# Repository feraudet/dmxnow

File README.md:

# dmxnow

Wireless DMX and LED strip nodes over ESP-NOW, driven by QLC+ from a Raspberry Pi.
One mains cable per fixture: DMX arrives by radio, the node switches the fixture's
power and drives 4 LED strip channels.

Nœuds DMX et rubans LED sans fil, sur ESP-NOW, pilotés par QLC+ depuis un Raspberry Pi.
Un seul câble secteur par projecteur : le DMX arrive par radio, le nœud coupe
l'alimentation du projecteur et pilote 4 canaux de rubans LED.

| | |
|---|---|
| 🇬🇧 **[Read in English](README.en.md)** | context, the need, use cases, how it works, status |
| 🇫🇷 **[Lire en français](README.fr.md)** | contexte, besoin, cas d'usage, fonctionnement, état du projet |

🔴 230 V mains device: read [docs/securite.md](docs/securite.md) first.
Appareil raccordé au 230 V : lire [docs/securite.md](docs/securite.md) avant tout.

Hardware CERN-OHL-S-2.0, software GPL-3.0-or-later: [LICENSE](LICENSE).

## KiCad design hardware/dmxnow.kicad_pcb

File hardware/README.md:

# dmxnow : matériel

PCB du nœud : 2 couches, cuivre 2 oz, **146 × 54 mm** plus une bande de 47,5 × 11,5 mm
au-dessus de la zone 230 V (porte-fusible F1), séparation à X = 100 mm par fente fraisée
et trois languettes perforées (partie principale « projecteur » 100 × 54 mm, partie
sécable « rubans » 46 × 54 mm). Révision 0.3 (après revue de conception, voir
`REVIEW.md`).

> 🔴 Carte manipulant du 230 V : lire et compléter [REVIEW.md](REVIEW.md) avant toute
> commande ou mise sous tension. Les cotes de K1 (Omron G5RL-1A-E-HR), des borniers WAGO
> 2604 et de PS1 (Mean Well IRM-03-5) ont été relevées sur les fiches constructeur
> ([datasheets/README.md](datasheets/README.md)) ; leur contrôle fait partie de la relecture.

## Contenu

| Fichier | Rôle |
|---------|------|
| `gen/design.py` | **Source unique** : composants, empreintes, broches → nets, classes de nets |
| `gen/footprints.py` | Empreintes du projet (`lib/dmxnow.pretty`), cotes et sources dans `DIMS` |
| `gen/sch.py` | Génère `dmxnow.kicad_sch` (schéma à étiquettes, symboles embarqués) |
| `gen/project.py` | Génère `dmxnow.kicad_pro` (classes de nets) et `dmxnow.kicad_dru` (règles 230 V) |
| `gen/pcb.py` | Génère `dmxnow.kicad_pcb` : contour, fentes, languettes perforées, placement, routage 230 V et LED, plans |
| `gen/route.py` | Routage des signaux basse tension par Freerouting, vias d'échappement et de couture GND |
| `gen/fixup.py` | Passe de finition : ferme les liaisons laissées par le routeur (segments directs, vias vers les plans) |
| `gen/vendor.py` | Copie figée des symboles et empreintes KiCad utilisés (`lib/vendor/`) |
| `gen/check.py` | Contrôles de cohérence : netlist du schéma, pastilles du PCB, traversée de la découpe |
| `gen/drc.py` | DRC local via l'API pcbnew (KiCad 7+) |
| `gen/fab.py` | Sorties JLCPCB dans `fab/` |
| `lib/` | Bibliothèques : `dmxnow.pretty`, `Espressif.*` (espressif/kicad-libraries, CC-BY-SA 4.0) |
| `REVIEW.md` | Liste de contrôle de la relecture humaine |
| `revision-suivante.md` | Points à intégrer à la prochaine révision du PCB |

Ne pas éditer les fichiers KiCad à la main : modifier les scripts et régénérer (un
changement manuel serait écrasé et rendrait la CI rouge).

## Régénérer

Prérequis : KiCad ≥ 7 (module Python `pcbnew`, `kicad-cli`), Java ≥ 17, Freerouting
(`FREEROUTING_JAR`, défaut `/opt/freerouting/freerouting.jar`).

```sh
cd hardware
make lib sch project   # empreintes, schéma, projet et règles
make pcb route         # PCB puis routage automatique + finition (~15 min)
make check             # netlist, cohérence PCB, DRC local
make fab               # Gerbers, perçages, BOM/CPL JLCPCB
```

`make pcb` repart de zéro : il faut relancer `make route` ensuite (ou `make reimport`
pour réappliquer la dernière session Freerouting si aucun composant n'a bougé).
Freerouting n'est pas déterministe : deux passages donnent des routages différents,
toujours validés par `make check`.

## Contrôles

- **Local** (KiCad 7) : `make check` (netlist schéma = `design.py`, pastilles PCB =
  `design.py`, seuls PWM1-4, BOARD_SENSE, +5V, GND traversent la découpe et uniquement
  sur les languettes, aucune piste 230 V au-delà de X = 46 mm, aucun via dans une
  pastille CMS, DRC, puis `gen/drc_canary.py` : des défauts injectés doivent déclencher
  chaque règle 230 V, preuve que les règles personnalisées sont chargées).
- **CI** (`.github/workflows/hardware.yml`, KiCad 9) : fichiers générés à jour, ERC, DRC
  avec parité schéma/PCB, sorties de fabrication, rendus 3D dessus/dessous (artefact
  `dmxnow-hardware`).

## Règles d'isolement (🔴)

Définies dans `gen/project.py` → `dmxnow.kicad_dru` :

| Règle | Valeur |
|-------|--------|
| Cuivre 230 V ↔ tout autre cuivre ou trou | ≥ 6 mm |
| Entre nets 230 V | ≥ 3 mm |
| Pastilles internes de K1 (COM/NO) et de PS1 (AC) | ≥ 2 mm (imposé par le composant) |
| Cuivre 230 V ↔ bord de carte | ≥ 1 mm |

Géométrie : cuivre 230 V à X ≤ 46 mm, basse tension à X ≥ 52 mm, fentes de 1,2 mm à
X = 49 mm sous K1 et PS1, aucun cuivre à moins de 6 mm de la pastille NC de PS1 (rangée
AC du module). Aucun trou de fixation dans la zone 230 V. Le PE ne passe pas
par la carte (WAGO 221-413 dans le boîtier, arbitrage A9).

## Commande JLCPCB

Dossier pas à pas (réglages, remarque, aperçu, achats hors JLCPCB) : [`ORDER.md`](ORDER.md).

- `fab/dmxnow-gerbers.zip` : 2 couches, 1,6 mm, **2 oz**, FR-4 TG ≥ 150.
- Séparation : fente et perforations sont dans les Gerbers (Edge.Cuts, NPTH). JLCPCB
  compte la carte comme **2 designs** : « Different Design = 2 », « Panel by Customer »
  1×1, « Remove order number = Yes ». Remarque de commande :
  « One circuit with an internal routed slot and 3 breakaway tabs carrying traces; deliver and assemble as one piece, do NOT separate. SMT: convey on the straight short edges X=0 and X=146; U1/Q5/R10 are close to the Y=54 edge by design. J3, J2 not populated: keep holes open (no solder fill). J1, J4, J7, J5, J6, J8: wire entry toward board edge; J6 and J8 side by side. RV1: form leads to the PCB holes. F2: press flat before soldering. F1/F2 fuses are not fitted. »
- Assemblage complet (CMS + traversants, PCBA « Standard ») : `fab/bom_jlcpcb_full.csv`
  + `fab/cpl_jlcpcb_full.csv` ; CMS seuls (PCBA « Economic », traversants à la main) :
  `*_smt.csv`. Suffixe `_led` : avec la LED d'état (option A7). Positions et rotations
  converties aux conventions JLCPCB (`gen/fab.py`, `JLC_FIX`) ; contrôler l'aperçu de
  placement à la commande. Références LCSC vérifiées le 2026-09-26 (le WAGO 2604-1105 arrêté est
  remplacé par J6 2604-1102 + J8 2604-1103). La cartouche de F1 (Littelfuse 0215.500MXP) et le fusible de F2
  sont à insérer à la main.
- Composants traversants et hors carte : `fab/bom_full.csv`.

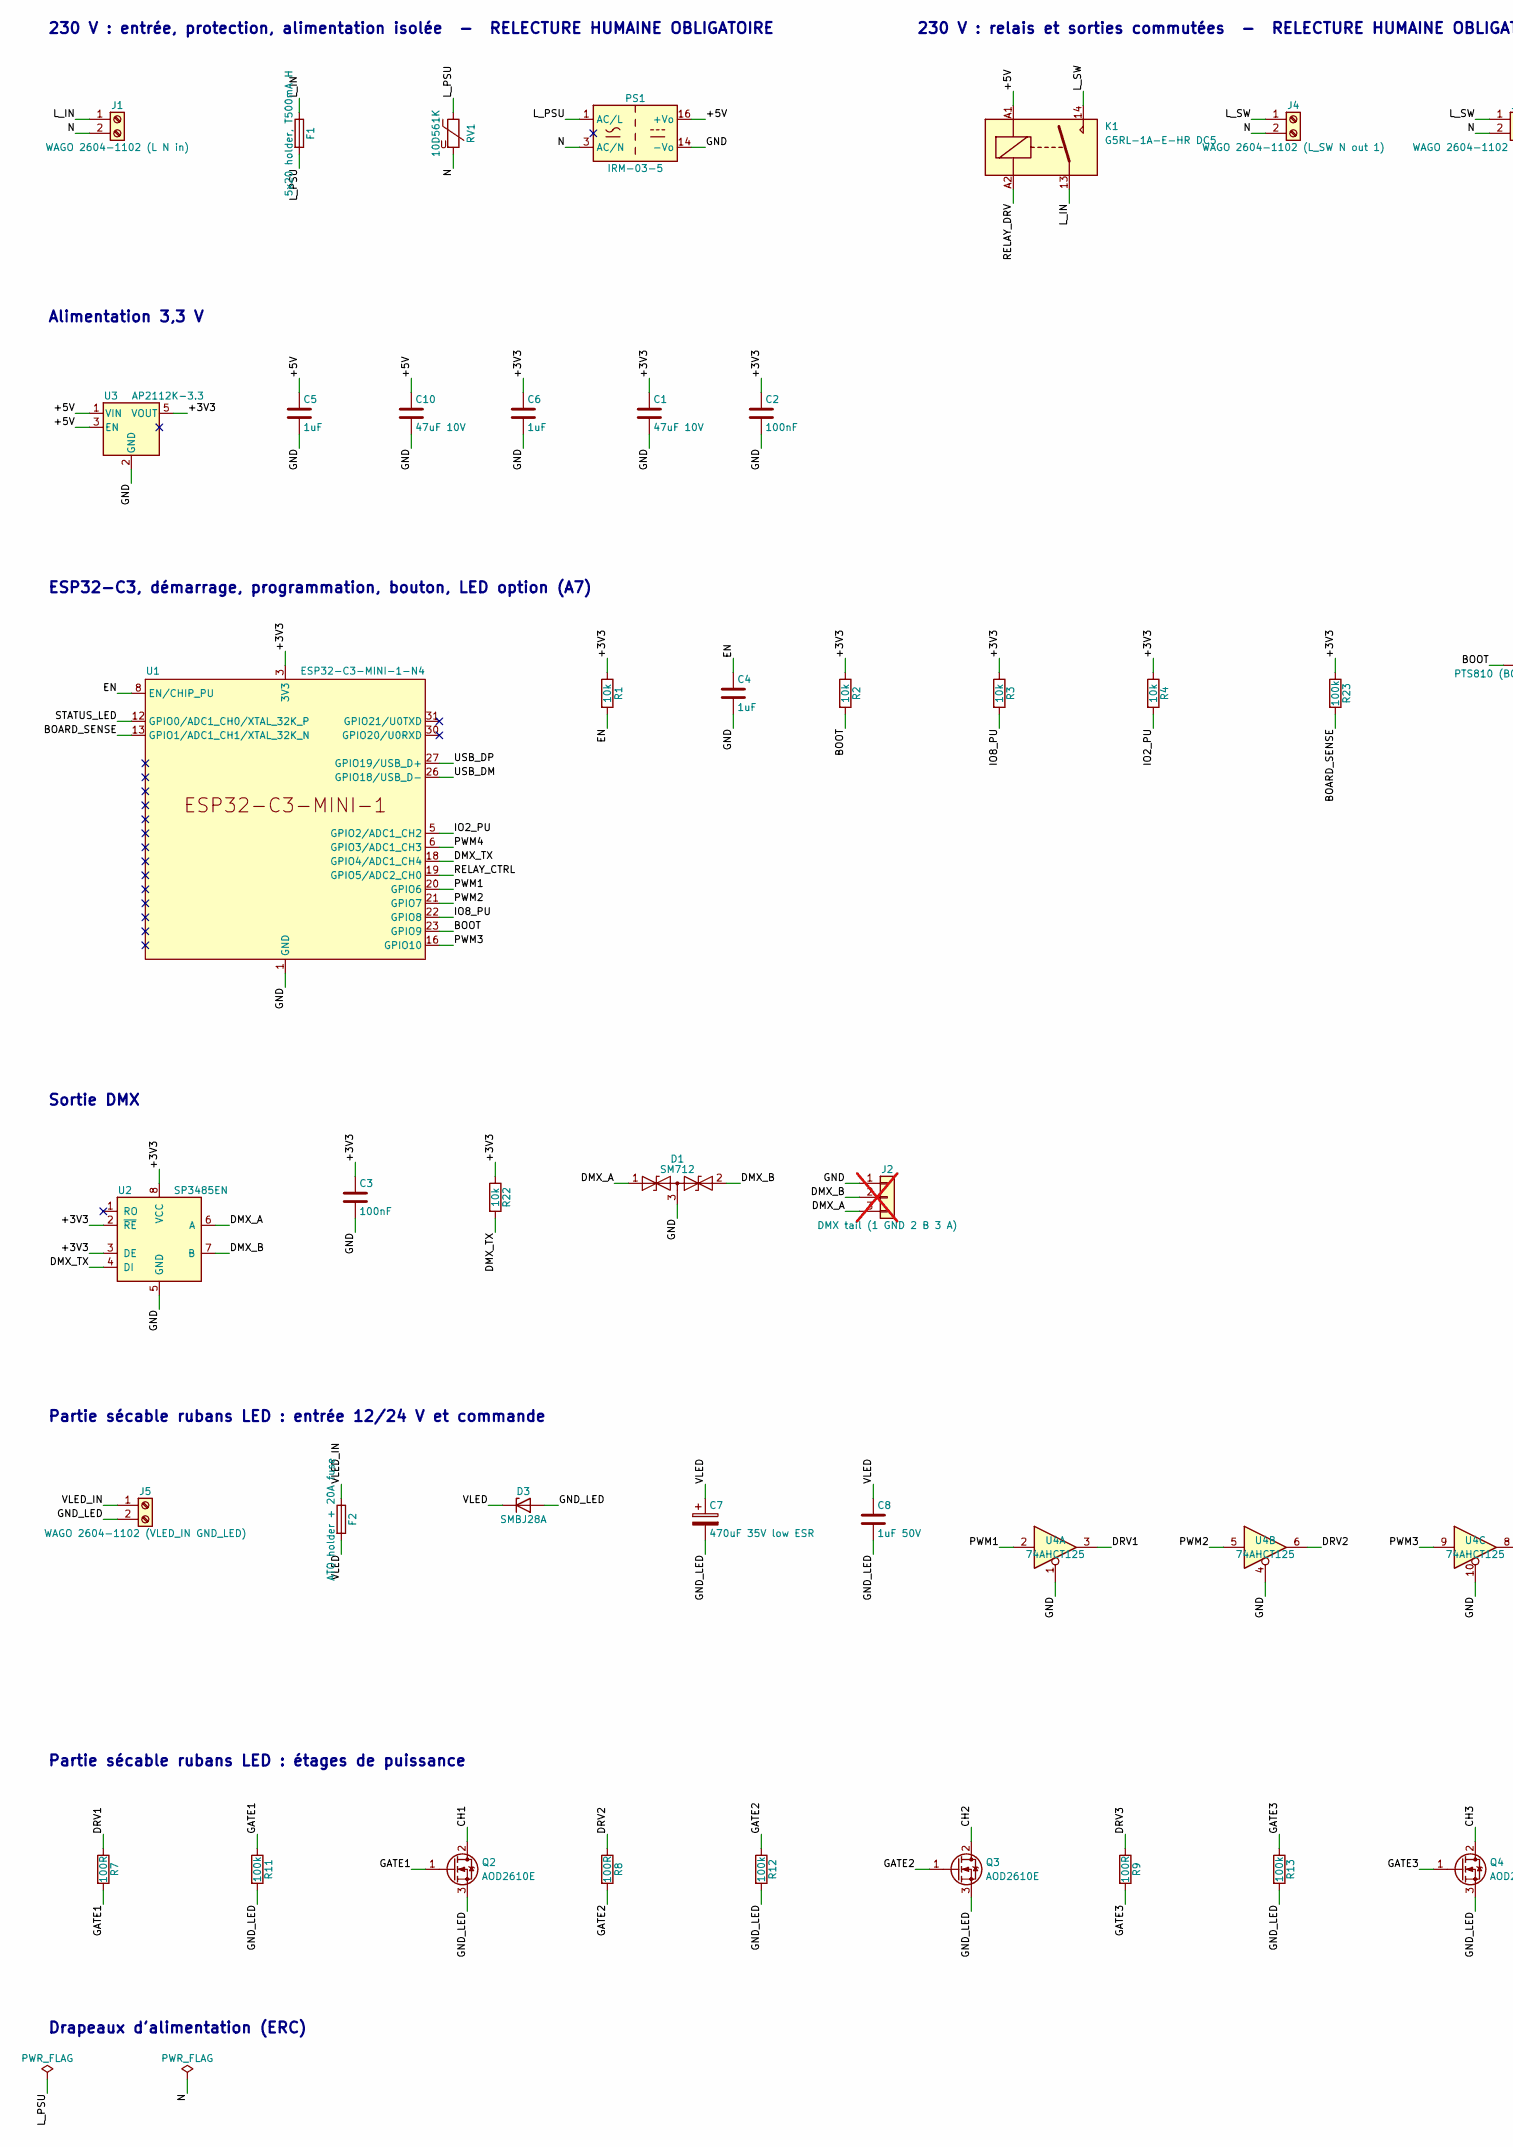
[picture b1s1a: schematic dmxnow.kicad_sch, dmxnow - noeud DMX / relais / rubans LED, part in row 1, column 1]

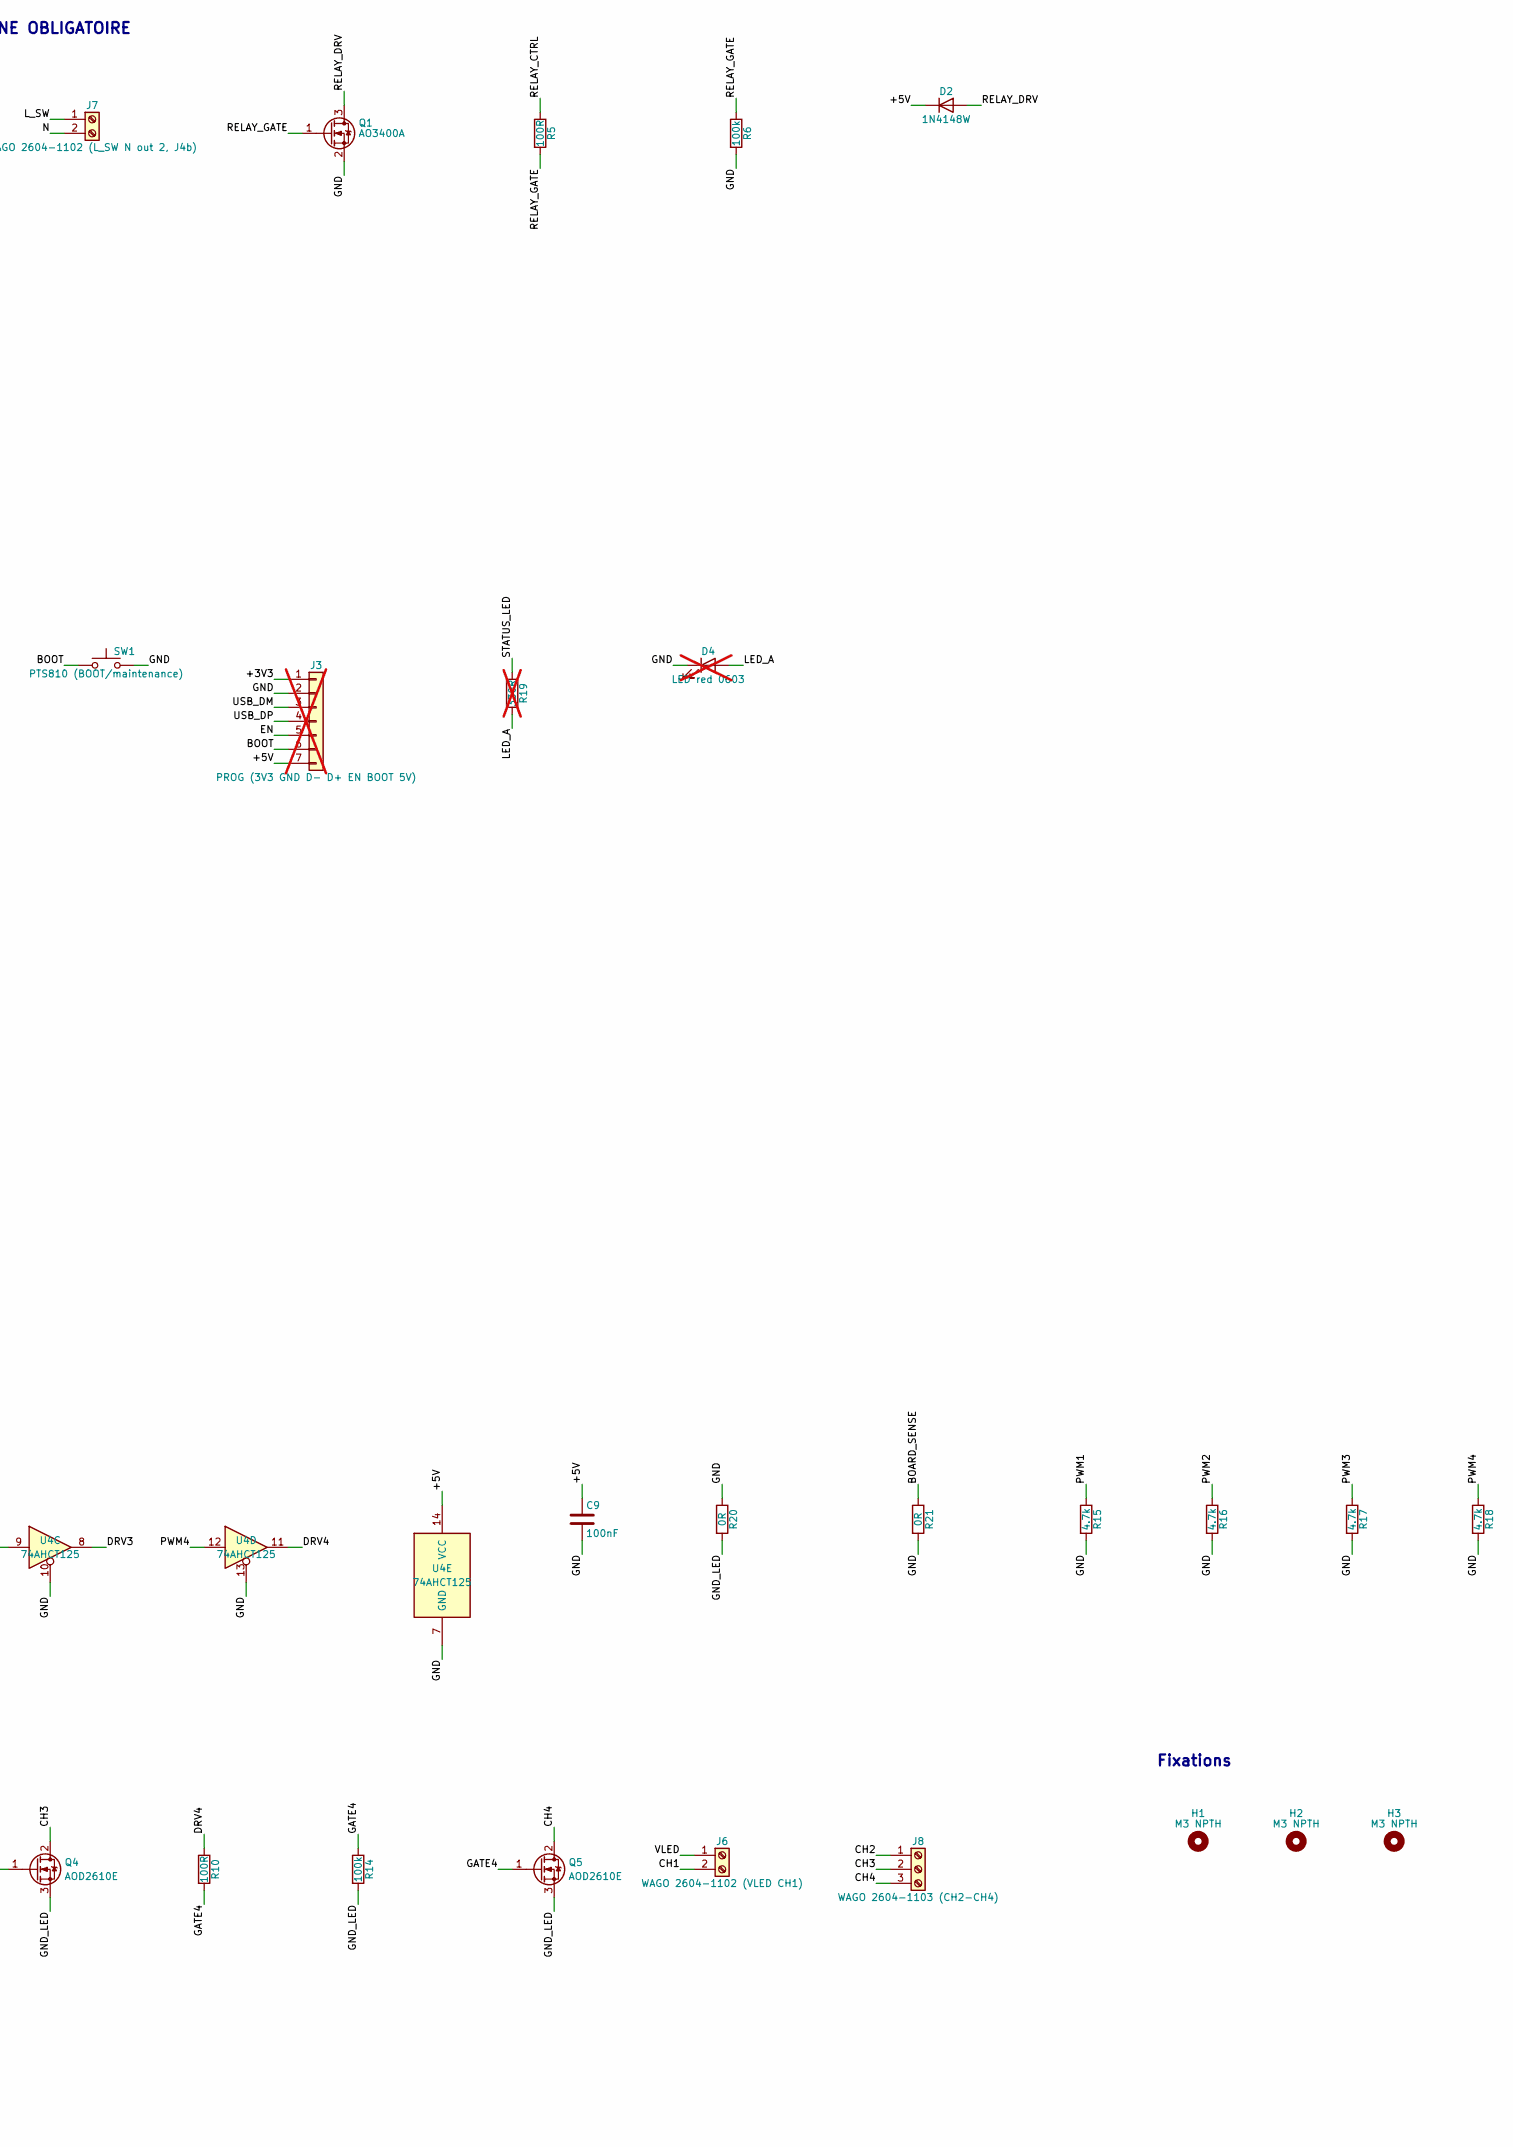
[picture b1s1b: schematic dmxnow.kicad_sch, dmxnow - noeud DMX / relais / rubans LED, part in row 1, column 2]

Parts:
C1, C10: 47uF 10V; C_1206_3216Metric; LCSC C96123
C2, C3, C9: 100nF; C_0603_1608Metric; LCSC C14663
C4, C5, C6: 1uF; C_0603_1608Metric; LCSC C15849
C7: 470uF 35V low ESR; CP_Radial_D10.0mm_P5.00mm; MPN Nichicon UHW1V471MPD; LCSC C136284
C8: 1uF 50V; C_1206_3216Metric; LCSC C1848
D1: SM712; SOT-23; MPN SM712.TCT; LCSC C12067
D2: 1N4148W; D_SOD-123; LCSC C81598
D3: SMBJ28A; D_SMB; MPN SMBJ28A; LCSC C113997
D4: LED red 0603; LED_0603_1608Metric; MPN KT-0603R; LCSC C2286; not fitted
F1: 5x20 holder, T500mA H; Fuseholder_Cylinder-5x20mm_Schurter_0031_8201_Horizontal_Op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; MPN Schurter 0031.8201; LCSC C3204125
F2: ATO holder + 20A fuse; FuseHolder_Blade_ATO_Littelfuse_FLR_178.6165; MPN Littelfuse 178.6165.0002; LCSC C207061
H1, H2, H3: M3 NPTH; MountingHole_3.2mm_M3
J1: WAGO 2604-1102 (L N in); TerminalBlock_WAGO_2604-1102_1x02_P5.00mm_Horizontal; MPN 2604-1102; LCSC C3309286
J2: DMX tail (1 GND 2 B 3 A); SolderWire-0.25sqmm_1x03_P4.2mm_D0.65mm_OD1.7mm; not fitted
J3: PROG (3V3 GND D- D+ EN BOOT 5V); PinHeader_1x07_P2.54mm_Vertical; not fitted
J4: WAGO 2604-1102 (L_SW N out 1); TerminalBlock_WAGO_2604-1102_1x02_P5.00mm_Horizontal; MPN 2604-1102; LCSC C3309286
J5: WAGO 2604-1102 (VLED_IN GND_LED); TerminalBlock_WAGO_2604-1102_1x02_P5.00mm_Horizontal; MPN 2604-1102; LCSC C3309286
J6: WAGO 2604-1102 (VLED CH1); TerminalBlock_WAGO_2604-1102_1x02_P5.00mm_Horizontal; MPN 2604-1102; LCSC C3309286
J7: WAGO 2604-1102 (L_SW N out 2, J4b); TerminalBlock_WAGO_2604-1102_1x02_P5.00mm_Horizontal; MPN 2604-1102; LCSC C3309286
J8: WAGO 2604-1103 (CH2-CH4); TerminalBlock_WAGO_2604-1103_1x03_P5.00mm_Horizontal; MPN 2604-1103; LCSC C3309758
K1: G5RL-1A-E-HR DC5; Relay_SPST_Omron_G5RL-1A-E-HR; MPN Omron G5RL-1A-E-HR DC5; LCSC C113250
PS1: IRM-03-5; Converter_ACDC_MeanWell_IRM-03-xx_THT_Drill1.0; MPN MEAN WELL IRM-03-5; LCSC C6969425
Q1: AO3400A; SOT-23; LCSC C20917
Q2, Q3, Q4, Q5: AOD2610E; TO-252-2; MPN AOD2610E; LCSC C282428
R1, R2, R3, R4, R22: 10k; R_0603_1608Metric; LCSC C25804
R5, R7, R8, R9, R10: 100R; R_0603_1608Metric; LCSC C22775
R6, R11, R12, R13, R14, R23: 100k; R_0603_1608Metric; LCSC C25803
R15, R16, R17, R18: 4.7k; R_0603_1608Metric; LCSC C23162
R19: 330R; R_0603_1608Metric; LCSC C23138; not fitted
R20: 0R; R_0805_2012Metric; LCSC C17477
R21: 0R; R_0603_1608Metric; LCSC C21189
RV1: 10D561K; RV_Disc_D12mm_T9mm_P7.5mm_Drill1.1; MPN 10D561K; LCSC C113236
SW1: PTS810 (BOOT/maintenance); SW_SPST_PTS810; MPN C&K PTS810 SJM 250 SMTR LFS; LCSC C116501
U1: ESP32-C3-MINI-1-N4; ESP32-C3-MINI-1; MPN ESP32-C3-MINI-1-N4; LCSC C2838502
U2: SP3485EN; SOIC-8_3.9x4.9mm_P1.27mm; MPN SP3485EN-L/TR; LCSC C8963
U3: AP2112K-3.3; SOT-23-5; MPN AP2112K-3.3TRG1; LCSC C51118
U4: 74AHCT125; SOIC-14_3.9x8.7mm_P1.27mm; MPN SN74AHCT125DR; LCSC C155176

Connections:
+3V3: C1.1, C2.1, C3.1, C6.1, J3.1, R1.1, R2.1, R3.1, R4.1, R22.1, R23.1, U1.3 (3V3), U2.2 (~RE), U2.3 (DE), U2.8 (VCC), U3.5 (VOUT)
+5V: C5.1, C9.1, C10.1, D2.1 (K), J3.7, K1.A1, PS1.16 (+Vo), U3.1 (VIN), U3.3 (EN), U4.14 (VCC)
BOARD_SENSE: R21.1, R23.2, U1.13 (GPIO1/ADC1_CH1/XTAL_32K_N)
BOOT: J3.6, R2.2, SW1.1, U1.23 (GPIO9)
CH1: J6.2, Q2.2 (D)
CH2: J8.1, Q3.2 (D)
CH3: J8.2, Q4.2 (D)
CH4: J8.3, Q5.2 (D)
DMX_A: D1.1 (A1), J2.3, U2.6 (A)
DMX_B: D1.2 (A2), J2.2, U2.7 (B)
DMX_TX: R22.2, U1.18 (GPIO4/ADC1_CH4), U2.4 (DI)
DRV1: R7.1, U4.3
DRV2: R8.1, U4.6
DRV3: R9.1, U4.8
DRV4: R10.1, U4.11
EN: C4.1, J3.5, R1.2, U1.8 (EN/CHIP_PU)
GATE1: Q2.1 (G), R7.2, R11.1
GATE2: Q3.1 (G), R8.2, R12.1
GATE3: Q4.1 (G), R9.2, R13.1
GATE4: Q5.1 (G), R10.2, R14.1
GND: C1.2, C2.2, C3.2, C4.2, C5.2, C6.2, C9.2, C10.2, D1.3 (common), D4.1 (K), J2.1, J3.2, PS1.14 (-Vo), Q1.2 (S), R6.2, R15.2, R16.2, R17.2, R18.2, R20.1, R21.2, SW1.2, U1.1 (GND), U1.2 (GND), U1.11 (GND), U1.14 (GND), U1.36 (GND), U1.37 (GND), U1.38 (GND), U1.39 (GND), U1.40 (GND), U1.41 (GND), U1.42 (GND), U1.43 (GND), U1.44 (GND), U1.45 (GND), U1.46 (GND), U1.47 (GND), U1.48 (GND), U1.49 (GND), U1.50 (GND), U1.51 (GND), U1.52 (GND), U1.53 (GND), U2.5 (GND), U3.2 (GND), U4.1, U4.4, U4.7 (GND), U4.10, U4.13
GND_LED: C7.2, C8.2, D3.2 (A), J5.2, Q2.3 (S), Q3.3 (S), Q4.3 (S), Q5.3 (S), R11.2, R12.2, R13.2, R14.2, R20.2
IO2_PU: R4.2, U1.5 (GPIO2/ADC1_CH2)
IO8_PU: R3.2, U1.22 (GPIO8)
LED_A: D4.2 (A), R19.2
L_IN: F1.1, J1.1, K1.13
L_PSU: F1.2, PS1.1 (AC/L), RV1.1
L_SW: J4.1, J7.1, K1.14
N: J1.2, J4.2, J7.2, PS1.3 (AC/N), RV1.2
PWM1: R15.1, U1.20 (GPIO6), U4.2
PWM2: R16.1, U1.21 (GPIO7), U4.5
PWM3: R17.1, U1.16 (GPIO10), U4.9
PWM4: R18.1, U1.6 (GPIO3/ADC1_CH3), U4.12
RELAY_CTRL: R5.1, U1.19 (GPIO5/ADC2_CH0)
RELAY_DRV: D2.2 (A), K1.A2, Q1.3 (D)
RELAY_GATE: Q1.1 (G), R5.2, R6.1
STATUS_LED: R19.1, U1.12 (GPIO0/ADC1_CH0/XTAL_32K_P)
USB_DM: J3.3, U1.26 (GPIO18/USB_D-)
USB_DP: J3.4, U1.27 (GPIO19/USB_D+)
VLED: C7.1, C8.1, D3.1 (K), F2.2, J6.1
VLED_IN: F2.1, J5.1

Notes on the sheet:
230 V : entrée, protection, alimentation isolée - RELECTURE HUMAINE OBLIGATOIRE
230 V : relais et sorties commutées - RELECTURE HUMAINE OBLIGATOIRE
Alimentation 3,3 V
ESP32-C3, démarrage, programmation, bouton, LED option (A7)
Sortie DMX
Partie sécable rubans LED : entrée 12/24 V et commande
Partie sécable rubans LED : étages de puissance
Fixations
Drapeaux d'alimentation (ERC)

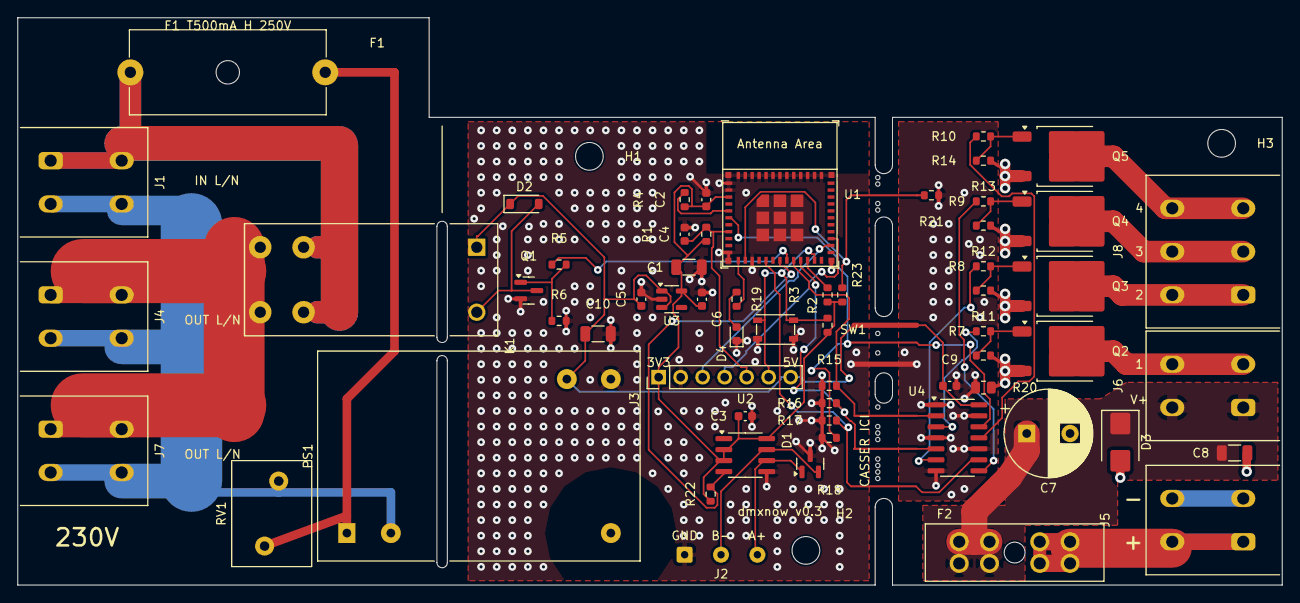
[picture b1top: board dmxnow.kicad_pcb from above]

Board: 2 copper layers, 146.0 x 65.5 mm, 77 parts (0 on the bottom side), 41 nets.

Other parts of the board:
MB: (no value)
MB#2, MB#3, MB#4, MB#5, MB#6, MB#7, MB#8, MB#9, MB#10, MB#11, MB#12, MB#13, MB#14: (no value)

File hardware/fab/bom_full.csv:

Ref,Value,Footprint,MPN,LCSC,Section,Fitted,Assembly,Note
J1,WAGO 2604-1102 (L N in),dmxnow:TerminalBlock_WAGO_2604-1102_1x02_P5.00mm_Horizontal,2604-1102,C3309286,main,yes,THT,PE is joined off-board by a WAGO 221-413 (arbitrage A9)
J4,WAGO 2604-1102 (L_SW N out 1),dmxnow:TerminalBlock_WAGO_2604-1102_1x02_P5.00mm_Horizontal,2604-1102,C3309286,main,yes,THT,PE is joined off-board by a WAGO 221-413 (arbitrage A9)
J7,"WAGO 2604-1102 (L_SW N out 2, J4b)",dmxnow:TerminalBlock_WAGO_2604-1102_1x02_P5.00mm_Horizontal,2604-1102,C3309286,main,yes,THT,PE is joined off-board by a WAGO 221-413 (arbitrage A9)
F1,"5x20 holder, T500mA H",Fuse:Fuseholder_Cylinder-5x20mm_Schurter_0031_8201_Horizontal_Open,Schurter 0031.8201,C3204125,main,yes,THT,"Fuse: Littelfuse 0215.500MXP (T500mA 250V ceramic, 1500 A)"
RV1,10D561K,dmxnow:RV_Disc_D12mm_T9mm_P7.5mm_Drill1.1,10D561K,C113236,main,yes,THT,
PS1,IRM-03-5,dmxnow:Converter_ACDC_MeanWell_IRM-03-xx_THT_Drill1.0,MEAN WELL IRM-03-5,C6969425,main,yes,THT,
K1,G5RL-1A-E-HR DC5,dmxnow:Relay_SPST_Omron_G5RL-1A-E-HR,Omron G5RL-1A-E-HR DC5,C113250,main,yes,THT,"Omron pins: coil 1/8, COM 3/6, NO 4/5"
U3,AP2112K-3.3,Package_TO_SOT_SMD:SOT-23-5,AP2112K-3.3TRG1,C51118,main,yes,SMT,
C5,1uF,Capacitor_SMD:C_0603_1608Metric,,C15849,main,yes,SMT,
C10,47uF 10V,Capacitor_SMD:C_1206_3216Metric,,C96123,main,yes,SMT,
C6,1uF,Capacitor_SMD:C_0603_1608Metric,,C15849,main,yes,SMT,
C1,47uF 10V,Capacitor_SMD:C_1206_3216Metric,,C96123,main,yes,SMT,
C2,100nF,Capacitor_SMD:C_0603_1608Metric,,C14663,main,yes,SMT,
U1,ESP32-C3-MINI-1-N4,Espressif:ESP32-C3-MINI-1,ESP32-C3-MINI-1-N4,C2838502,main,yes,SMT,
R1,10k,Resistor_SMD:R_0603_1608Metric,,C25804,main,yes,SMT,
C4,1uF,Capacitor_SMD:C_0603_1608Metric,,C15849,main,yes,SMT,
R2,10k,Resistor_SMD:R_0603_1608Metric,,C25804,main,yes,SMT,
R3,10k,Resistor_SMD:R_0603_1608Metric,,C25804,main,yes,SMT,
R4,10k,Resistor_SMD:R_0603_1608Metric,,C25804,main,yes,SMT,
SW1,PTS810 (BOOT/maintenance),Button_Switch_SMD:SW_SPST_PTS810,C&K PTS810 SJM 250 SMTR LFS,C116501,main,yes,SMT,
J3,PROG (3V3 GND D- D+ EN BOOT 5V),Connector_PinHeader_2.54mm:PinHeader_1x07_P2.54mm_Vertical,,,main,no,THT,"Pads only, header not fitted"
R19,330R,Resistor_SMD:R_0603_1608Metric,,C23138,main,DNP (option A7),SMT,
D4,LED red 0603,LED_SMD:LED_0603_1608Metric,KT-0603R,C2286,main,DNP (option A7),SMT,
R5,100R,Resistor_SMD:R_0603_1608Metric,,C22775,main,yes,SMT,
R6,100k,Resistor_SMD:R_0603_1608Metric,,C25803,main,yes,SMT,
Q1,AO3400A,Package_TO_SOT_SMD:SOT-23,,C20917,main,yes,SMT,
D2,1N4148W,Diode_SMD:D_SOD-123,,C81598,main,yes,SMT,
U2,SP3485EN,Package_SO:SOIC-8_3.9x4.9mm_P1.27mm,SP3485EN-L/TR,C8963,main,yes,SMT,
C3,100nF,Capacitor_SMD:C_0603_1608Metric,,C14663,main,yes,SMT,
R22,10k,Resistor_SMD:R_0603_1608Metric,,C25804,main,yes,SMT,
D1,SM712,Package_TO_SOT_SMD:SOT-23,SM712.TCT,C12067,main,yes,SMT,
J2,DMX tail (1 GND 2 B 3 A),Connector_Wire:SolderWire-0.25sqmm_1x03_P4.2mm_D0.65mm_OD1.7mm,,,main,no,THT,Wire pads
J5,WAGO 2604-1102 (VLED_IN GND_LED),dmxnow:TerminalBlock_WAGO_2604-1102_1x02_P5.00mm_Horizontal,2604-1102,C3309286,strip,yes,THT,
F2,ATO holder + 20A fuse,Fuse:FuseHolder_Blade_ATO_Littelfuse_FLR_178.6165,Littelfuse 178.6165.0002,C207061,strip,yes,THT,
D3,SMBJ28A,Diode_SMD:D_SMB,SMBJ28A,C113997,strip,yes,SMT,
C7,470uF 35V low ESR,Capacitor_THT:CP_Radial_D10.0mm_P5.00mm,Nichicon UHW1V471MPD,C136284,strip,yes,THT,2 A ripple at 100 kHz (V-HW-08)
C8,1uF 50V,Capacitor_SMD:C_1206_3216Metric,,C1848,strip,yes,SMT,
U4,74AHCT125,Package_SO:SOIC-14_3.9x8.7mm_P1.27mm,SN74AHCT125DR,C155176,strip,yes,SMT,
C9,100nF,Capacitor_SMD:C_0603_1608Metric,,C14663,strip,yes,SMT,
J6,WAGO 2604-1102 (VLED CH1),dmxnow:TerminalBlock_WAGO_2604-1102_1x02_P5.00mm_Horizontal,2604-1102,C3309286,strip,yes,THT,
J8,WAGO 2604-1103 (CH2-CH4),dmxnow:TerminalBlock_WAGO_2604-1103_1x03_P5.00mm_Horizontal,2604-1103,C3309758,strip,yes,THT,
R20,0R,Resistor_SMD:R_0805_2012Metric,,C17477,strip,yes,SMT,Logic ground to LED ground star point
R21,0R,Resistor_SMD:R_0603_1608Metric,,C21189,strip,yes,SMT,Variant detection (GPIO1 low = strip part present)
R23,100k,Resistor_SMD:R_0603_1608Metric,,C25803,main,yes,SMT,
R15,4.7k,Resistor_SMD:R_0603_1608Metric,,C23162,main,yes,SMT,"PWM pull-down, main side of the breakaway line, SPEC 4.6"
R7,100R,Resistor_SMD:R_0603_1608Metric,,C22775,strip,yes,SMT,
R11,100k,Resistor_SMD:R_0603_1608Metric,,C25803,strip,yes,SMT,
Q2,AOD2610E,Package_TO_SOT_SMD:TO-252-2,AOD2610E,C282428,strip,yes,SMT,60 V: above the SMBJ28A clamp voltage (R-10)
R16,4.7k,Resistor_SMD:R_0603_1608Metric,,C23162,main,yes,SMT,"PWM pull-down, main side of the breakaway line, SPEC 4.6"
R8,100R,Resistor_SMD:R_0603_1608Metric,,C22775,strip,yes,SMT,
R12,100k,Resistor_SMD:R_0603_1608Metric,,C25803,strip,yes,SMT,
Q3,AOD2610E,Package_TO_SOT_SMD:TO-252-2,AOD2610E,C282428,strip,yes,SMT,60 V: above the SMBJ28A clamp voltage (R-10)
R17,4.7k,Resistor_SMD:R_0603_1608Metric,,C23162,main,yes,SMT,"PWM pull-down, main side of the breakaway line, SPEC 4.6"
R9,100R,Resistor_SMD:R_0603_1608Metric,,C22775,strip,yes,SMT,
R13,100k,Resistor_SMD:R_0603_1608Metric,,C25803,strip,yes,SMT,
Q4,AOD2610E,Package_TO_SOT_SMD:TO-252-2,AOD2610E,C282428,strip,yes,SMT,60 V: above the SMBJ28A clamp voltage (R-10)
R18,4.7k,Resistor_SMD:R_0603_1608Metric,,C23162,main,yes,SMT,"PWM pull-down, main side of the breakaway line, SPEC 4.6"
R10,100R,Resistor_SMD:R_0603_1608Metric,,C22775,strip,yes,SMT,
R14,100k,Resistor_SMD:R_0603_1608Metric,,C25803,strip,yes,SMT,
Q5,AOD2610E,Package_TO_SOT_SMD:TO-252-2,AOD2610E,C282428,strip,yes,SMT,60 V: above the SMBJ28A clamp voltage (R-10)
-,WAGO 221-413,-,221-413,,full+cut,x1,off-board,"PE junction, 230 V compartment (arbitrage A9)"
-,ATO blade fuse 20 A,-,Littelfuse 0257020,,full,x1,off-board,"F2 fuse (<= 80 % continuous load, see REVIEW.md)"
-,Fuse 5x20 T500mA H 250V ceramic,-,Littelfuse 0215.500MXP,,full+cut,x1,off-board,"F1 cartridge, into the F1 holder (LCSC C142839)"
-,Neutrik NC3FXX,-,NC3FXX,,full+cut,x1,off-board,DMX tail connector
-,"DMX cable 120 ohm, 1 m",-,,,full+cut,x1,off-board,DMX tail
-,Cable gland M16 (or PG9),-,,,full+cut,x3,off-board,"mains in, projector out, LED PSU out"
-,Cable gland PG7,-,,,full+cut,x3,off-board,DMX tail; LED in/out on full board
-,M3 heat-set insert + M3 nylon screw,-,,,full+cut,x6,off-board,PCB and lid fixing

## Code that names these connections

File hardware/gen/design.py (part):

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esp_pins.update({
    "3": "+3V3",
    "8": "EN",
    "12": "STATUS_LED",   # GPIO0, option A7
    "13": "BOARD_SENSE",  # GPIO1
    "5": "IO2_PU",        # GPIO2 strapping
    "6": "PWM4",          # GPIO3
    "18": "DMX_TX",       # GPIO4
    "19": "RELAY_CTRL",   # GPIO5
    "20": "PWM1",         # GPIO6
    "21": "PWM2",         # GPIO7
    "22": "IO8_PU",       # GPIO8 strapping
    "23": "BOOT",         # GPIO9 strapping / SW1
    "16": "PWM3",         # GPIO10
    "26": "USB_DM",       # GPIO18
    "27": "USB_DP",       # GPIO19
    "30": None,           # GPIO20 U0RXD, unused
    "31": None,           # GPIO21 U0TXD, unused
})
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         {"1": None, "2": "+3V3", "3": "+3V3", "4": "DMX_TX", "5": "GND", "6": "DMX_A",
          "7": "DMX_B", "8": "+3V3"}, lcsc="C8963", mpn="SP3485EN-L/TR"),
    C("C3", "100nF", "+3V3", "GND", lcsc="C14663"),
    # DMX_TX idles at mark while GPIO4 floats (reset, boot): the driver is always enabled
    R("R22", "10k", "+3V3", "DMX_TX", lcsc="C25804"),
    Part("D1", "Diode:SM712_SOT23", "Package_TO_SOT_SMD:SOT-23", "SM712",
         {"1": "DMX_A", "2": "DMX_B", "3": "GND"}, lcsc="C12067", mpn="SM712.TCT"),
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    Part("R20", "Device:R", "Resistor_SMD:R_0805_2012Metric", "0R", {"1": "GND", "2": "GND_LED"},
         lcsc="C17477", section="strip", note="Logic ground to LED ground star point"),
    Part("R21", "Device:R", FP_R, "0R", {"1": "BOARD_SENSE", "2": "GND"},
         lcsc="C21189", section="strip", note="Variant detection (GPIO1 low = strip part present)"),
    # BOARD_SENSE pull-up on the main side: reads high once the strip part is snapped off,
    # whatever the firmware does with the internal pull-up
    R("R23", "100k", "+3V3", "BOARD_SENSE", lcsc="C25803"),
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for i in range(4):
    n = i + 1
    PARTS += [
        # 4.7k: GPIO6 (PWM1) has a ~45k internal pull-up from reset until the firmware
        # takes the pin (ESP32-C3 datasheet table 2-1 note 6); keeps U4 inputs < 0.8 V
        R("R%d" % (15 + i), "4.7k", "PWM%d" % n, "GND", lcsc="C23162", section="main",
          note="PWM pull-down, main side of the breakaway line, SPEC 4.6"),
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
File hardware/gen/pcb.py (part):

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    # --- 230 V zone 🔴 ---------------------------------------------------
    "J1": (3.8, 5.0, -90),       # L_IN y=5, N y=10 ; wire entry towards -X
    "J4": (3.8, 20.5, -90),      # L_SW y=20.5, N y=25.5
    "J7": (3.8, 36.0, -90),      # L_SW y=36, N y=41
    "K1": (53.0, 15.0, -90),     # coil A1 (53,15) A2 (53,22.5) ; COM x=33 ; NO x=28
    "F1": (13.0, -5.2, 0),       # holder in the top band: pin1 L_IN (13,-5.2), pin2 L_PSU (35.5,-5.2)
    "PS1": (38.0, 48.0, 90),     # AC/L (38,48) AC/N (43.08,48) ; +Vo (63.4,30.22) -Vo (68.48,30.22)
    "RV1": (28.5, 49.5, 90),     # L_PSU (28.5,49.5) ; N (30.13,42) ; 9 mm thick body clear of PS1
    # --- low voltage, main part (X 52..96) -------------------------------
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    # --- breakaway strip part (X 104..146) -------------------------------
    "J6": (141.5, 33.5, 90),     # 2604-1102: VLED y=33.5, CH1 y=28.5 ; entry towards +X
    "J8": (141.5, 20.5, 90),     # 2604-1103: CH2..CH4 y=20.5,15.5,10.5 (8 mm from CH1: blocks side by side)
    "J5": (141.5, 49.0, 90),     # VLED_IN y=49, GND_LED y=44
    "F2": (121.5, 51.5, 180),    # pin1 VLED_IN x 118..121.5, pin2 VLED x 108.7..112.2
    "C7": (116.5, 36.5, 0),      # + (116.5,36.5) - (121.5,36.5)
    "D3": (127.3, 37.5, 270),    # vertical, left of J6: anode (GND_LED) at the bottom
    "C8": (140.5, 38.75, 0),     # between J6 and J5
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F, B = pcbnew.F_Cu, pcbnew.B_Cu

MAINS_ROUTES = [
    # L_IN: J1 pin 1 -> relay COM (x=33) and, up into the top band, F1 pin 1. Both layers.
    ("L_IN", F, 1.9, [(3.8, 5.0), (12.0, 5.0)]),
    ("L_IN", B, 1.9, [(3.8, 5.0), (12.0, 5.0)]),
    ("L_IN", F, 4.0, [(12.0, 3.0), (37.15, 3.0)]),
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    ("L_IN", B, 2.6, [(34.6, 22.5), (37.15, 22.5)]),
    ("L_IN", F, 2.5, [(13.0, -5.2), (13.0, 3.0)]),
    ("L_IN", B, 2.5, [(13.0, -5.2), (13.0, 3.0)]),
    # L_SW: J4 pin 1 and J7 pin 1 -> relay NO bus (x=25). 7.4 mm fingers on top (they
    # cross the N bus, which is on the bottom), 3.1 mm from the N pads of the terminals.
    ("L_SW", F, 1.9, [(3.8, 20.5), (12.0, 20.5)]),
    ("L_SW", F, 7.4, [(7.5, 17.75), (25.0, 17.75)]),
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    # N branch to RV1 and PS1 AC/N (internal supply only, fused by F1 on the L side)
    ("N", B, 1.0, [(18.5, 43.3), (30.13, 43.3), (43.08, 43.3), (43.08, 48.0)]),
    ("N", B, 1.0, [(30.13, 43.3), (30.13, 42.0)]),
    # L_PSU: F1 pin 2 (top band) -> PS1 AC/L, branch to RV1 pin 1
    ("L_PSU", F, 1.0, [(35.5, -5.2), (43.5, -5.2), (43.5, 27.0), (38.0, 32.5), (38.0, 48.0)]),
    ("L_PSU", F, 1.0, [(38.0, 46.0), (28.5, 49.5)]),
]

LED_ROUTES = [
    # VLED_IN: J5 pin 1 (front 141.5 / back 133.3, y=49) -> F2 pin 1 (x 118..121.5, y 49..51.5)
    ("VLED_IN", F, 1.9, [(141.5, 49.0), (133.3, 49.0)]),
    ("VLED_IN", B, 1.9, [(141.5, 49.0), (133.3, 49.0)]),
    ("VLED_IN", F, 4.5, [(133.3, 49.75), (121.5, 49.75)]),
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# D3 anode and C8 pin 2 to the GND_LED pour (bottom)
LED_ROUTES += [("GND_LED", F, 1.0, [(127.3, 39.65), (127.3, 41.6)]),
               ("GND_LED", F, 1.0, [(141.9, 38.75), (141.9, 40.9)])]
# VLED: F2 pin 2 -> C7 + (keeps the VLED pour in one piece whatever the autorouter does)
LED_ROUTES += [("VLED", F, 3.0, [(108.7, 49.0), (112.2, 49.0)]),
               ("VLED", F, 3.0, [(110.45, 49.0), (110.45, 45.5), (114.5, 41.5), (116.5, 38.5), (116.5, 36.5)])]

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    # LED return on the strip part, bottom layer
    strip = [(113.4, 0.3), (W - 0.3, 0.3), (W - 0.3, H - 0.3), (113.4, H - 0.3)]
    add_zone(board, "GND_LED", [B], strip, clearance=0.4, name="GND_LED", solid="tht_thermal")
    # VLED on the top layer: F2 pin 2 -> C7 / D3 / C8 -> J6 pin 1 (17 A path)
    add_zone(board, "VLED", [F], VLED_POLY, clearance=0.4, name="VLED", solid="tht_thermal", priority=1)
    # Logic ground of the strip part (U4, pull-downs, net ties), top layer only
    logic = [(SPLIT_X + SLOT_W / 2 + 0.7, 0.5), (113.2, 0.5), (113.2, 44.3), (SPLIT_X + SLOT_W / 2 + 0.7, 44.3)]
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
